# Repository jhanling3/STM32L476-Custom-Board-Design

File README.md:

# STM32L476-Custom-Board-Design

This is a custom STM32L476 Board designed in KiCad to practice placing the MCU on a custom circuit.  I had this PCB manufactured, assembled it, and flashed it to confirm functionality.

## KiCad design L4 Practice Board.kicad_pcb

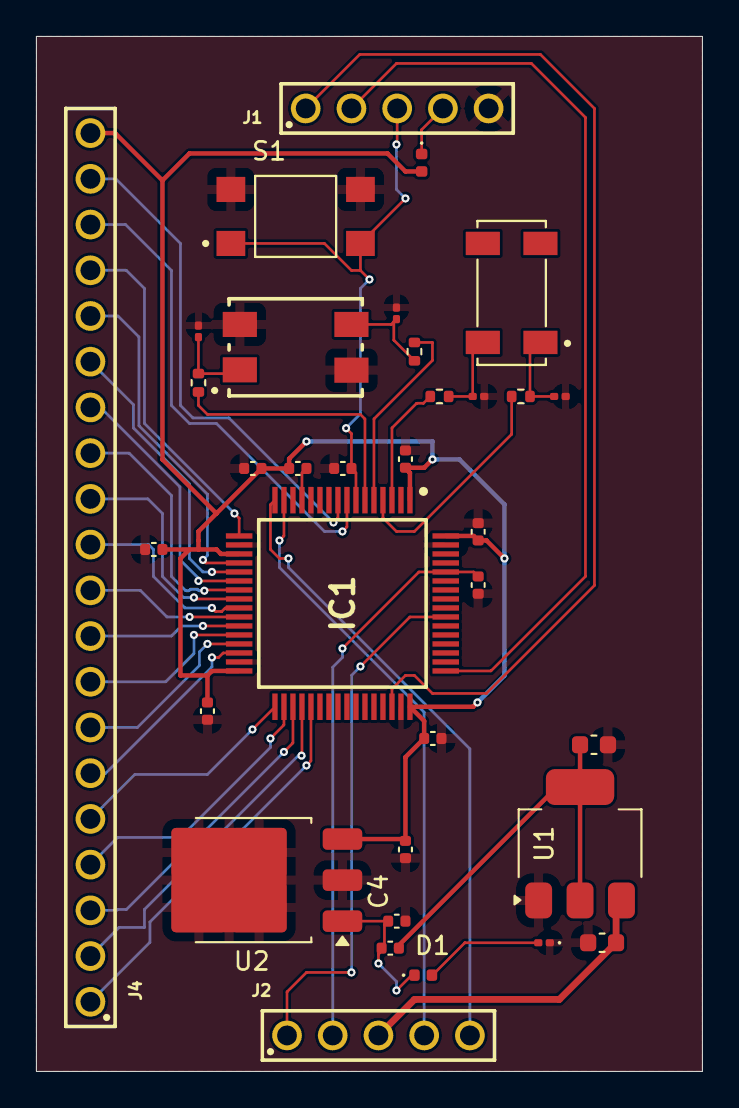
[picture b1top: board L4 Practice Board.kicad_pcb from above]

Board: 2 copper layers, 37.0 x 57.5 mm, 34 parts (0 on the bottom side), 42 nets.

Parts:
C1, C2: 10uF; C_0603_1608Metric
C3: 1uF; C_0402_1005Metric
C4: 2.2uF; C_0402_1005Metric
C5, C6, C7, C8, C9, C10, C11: 100nF; C_0402_1005Metric
C12, C13: 20pF; C_0201_0603Metric
C14, C15: 4.3pF; C_0201_0603Metric
D1: Power Diode; C_0402_1005Metric
D2: LED; D_0201_0603Metric
FB1: FerriteBead; C_0402_1005Metric
IC1: STM32L476RGT6; QFP50P1200X1200X160-64N
J1, J2: 6130XX11121_61300511121; 61300511121
J4: 6130XX11121_61302011121; 61302011121
R1, R7: 1k 0402; D_0402_1005Metric
R2: 10k; C_0402_1005Metric
R3, R4, R5, R6: 0k; R_0402_1005Metric
S1: TL3305AF160QG; SW_TL3305AF160QG
U1: LD1117S50TR_SOT223; SOT-223-3_TabPin2
U2: LD39150DT33; TO-252-3_TabPin2
Y1: LFXTAL026380; WE-XTAL_LFXTAL026380
Y2: ABS25-32.768KHZ-6-T; XTAL_ABS25-32.768KHZ-6-T

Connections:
+3.3V: C4.1, C5.1, C6.1, C7.1, C8.1, C9.1, C10.1, FB1.2, IC1.1 (VBAT), IC1.19 (VDD_1), IC1.32 (VDD_2), IC1.48 (VDDUSB), IC1.64 (VDD_3), J4.20, R7.2, U2.3 (VO)
+5V: C2.1, D1.2 (A), U1.2 (VO)
+15V: C1.1, J2.3, U1.3 (VI)
/PA3: IC1.17 (PA3), J4.17
/PA4: IC1.20 (PA4), J4.16
/PA5: IC1.21 (PA5), J4.15
/PA6: IC1.22 (PA6), J4.14
/PA7: IC1.23 (PA7), J4.13
/PB0: IC1.26 (PB0), J4.10
/PB1: IC1.27 (PB1), J4.9
/PB2: IC1.28 (PB2), J4.8
/PB10: IC1.29 (PB10), J4.7
/PB11: IC1.30 (PB11), J4.6
/PB12: IC1.33 (PB12), J4.5
/PB13: IC1.34 (PB13), J4.4
/PB14: IC1.35 (PB14), J4.3
/PB15: IC1.36 (PB15), J4.2
/PC0: IC1.8 (PC0), J4.18
/PC1: IC1.9 (PC1), J4.19
/PC4: IC1.24 (PC4), J4.12
/PC5: IC1.25 (PC5), J4.11
/PC6: IC1.37 (PC6), J4.1
BOOT0: IC1.60 (BOOT0), J2.2, R2.1
GND: C1.2, C2.2, C3.2, C4.2, C5.2, C6.2, C7.2, C8.2, C9.2, C10.2, C11.1, C12.1, C13.1, C14.1, C15.1, D2.1 (K), IC1.12 (VSSA/VREF-), IC1.18 (VSS_1), IC1.31 (VSS_2), IC1.47 (VSS_3), IC1.63 (VSS_4), J1.5, R2.2, S1.3, S1.4, U1.1 (GND), U2.2 (GND), Y1.2, Y1.4
NRST: C11.2, IC1.7 (NRST), J1.3, S1.1, S1.2
unnamed: C12.2, R3.1, Y1.3
unnamed: C13.2, R4.1, Y1.1
unnamed: C14.2, R5.1, Y2.4
unnamed: C15.2, R6.1, Y2.1
unnamed: C3.1, D1.1 (K), R1.1, U2.1 (VI)
unnamed: D2.2 (A), R1.2
unnamed: IC1.3 (PC14-OSC32_IN(PC14)), R5.2
unnamed: IC1.4 (PC15-OSC32_OUT(PC15)), R6.2
unnamed: IC1.5 (PH0-OSC_IN(PH0)), R3.2
unnamed: IC1.6 (PH1-OSC_OUT(PH1)), R4.2
unnamed: FB1.1, IC1.13 (VDDA/VREF+)
unnamed: J1.4, R7.1
SWCLK: IC1.49 (PA14(JTCK-SWCLK)), J1.2
SWDIO: IC1.46 (PA13(JTMS-SWDIO)), J1.1
SWO: IC1.55 (PB3(JTDO-TRACESWO)), J2.1
USART_RX: IC1.16 (PA2), J2.5
USART_TX: IC1.15 (PA1), J2.4

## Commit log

2026-01-11 KiCad Board Design STM32L4 Custom Board
2026-01-11 Add images to README for better visualization
    Added images to enhance the README documentation.
2026-01-11 Enhance README with project overview and images
    Added a brief overview of the STM32L476 custom board project, including manufacturing and assembly details.
